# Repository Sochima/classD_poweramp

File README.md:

# classD_poweramp
Schematic and PCB files of a 15 W stereo Class D power amplifier

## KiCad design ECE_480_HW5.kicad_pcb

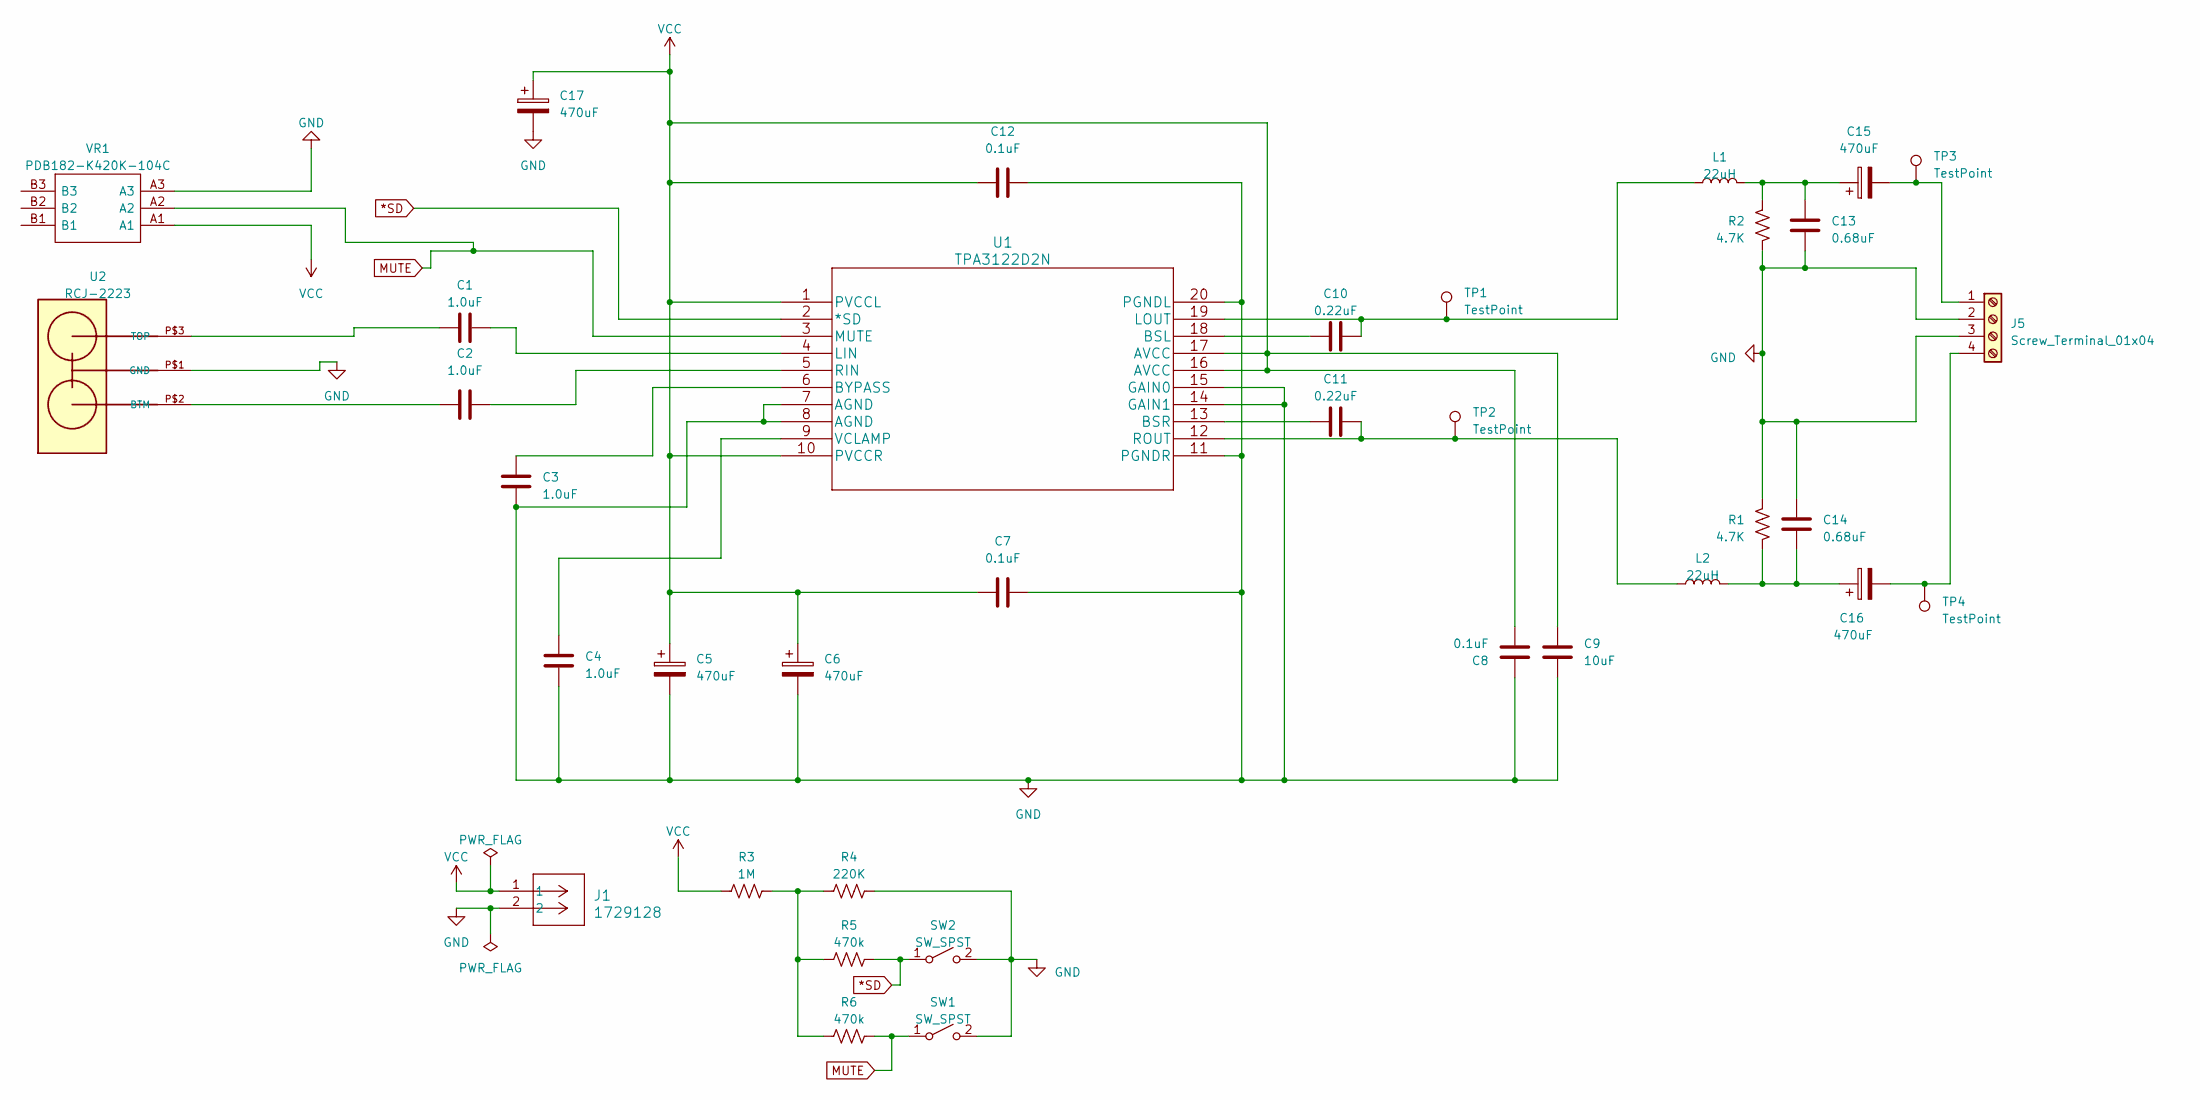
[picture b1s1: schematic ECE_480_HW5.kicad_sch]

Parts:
C1, C2, C3, C4: 1.0uF; CP_Axial_L10.0mm_D4.5mm_P15.00mm_Horizontal
C5, C6, C15, C16, C17: 470uF; CP_Radial_D7.5mm_P2.50mm
C7, C8, C12: 0.1uF; CP_Axial_L10.0mm_D4.5mm_P15.00mm_Horizontal
C9: 10uF; CP_Axial_L10.0mm_D4.5mm_P15.00mm_Horizontal
C10, C11: 0.22uF; CP_Axial_L10.0mm_D4.5mm_P15.00mm_Horizontal
C13, C14: 0.68uF; CP_Axial_L10.0mm_D4.5mm_P15.00mm_Horizontal
J1: 1729128; CONN_1729128_PXC
J5: Screw_Terminal_01x04; TerminalBlock_bornier-4_P5.08mm
L1, L2: 22uH; L_Axial_L16.0mm_D6.3mm_P20.32mm_Horizontal_Fastron_VHBCC
R1, R2: 4.7K; R_Axial_DIN0207_L6.3mm_D2.5mm_P10.16mm_Horizontal
R3: 1M; R_Axial_DIN0207_L6.3mm_D2.5mm_P10.16mm_Horizontal
R4: 220K; R_Axial_DIN0207_L6.3mm_D2.5mm_P10.16mm_Horizontal
R5, R6: 470k; R_Axial_DIN0207_L6.3mm_D2.5mm_P10.16mm_Horizontal
SW1, SW2: SW_SPST; SW_DIP_SPSTx01_Slide_9.78x4.72mm_W7.62mm_P2.54mm
TP1, TP2, TP3, TP4: TestPoint; TestPoint_THTPad_2.0x2.0mm_Drill1.0mm
U1: TPA3122D2N; N20
U2: RCJ-2223; DUALRCA
VR1: PDB182-K420K-104C; PDB182K420P204A2; Mouser Part Number 652-PDB182K420K104C

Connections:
*SD: R5.2, SW2.1 (A), U1.2 (*SD)
GND: C3.1, C4.2, C5.2, C6.2, C7.2, C8.1, C9.2, C12.2, C13.1, C14.2, C17.2, J1.2, J5.2, J5.3, R1.1, R2.2, R4.2, SW1.2 (B), SW2.2 (B), U1.7 (AGND), U1.8 (AGND), U1.11 (PGNDR), U1.14 (GAIN1), U1.15 (GAIN0), U1.20 (PGNDL), U2.P$1 (GND), VR1.A3
MUTE: R6.2, SW1.1 (A), U1.3 (MUTE), VR1.A2
unnamed: C13.2, C15.1, L1.2, R2.1
unnamed: C14.1, C16.1, L2.2, R1.2
unnamed: C15.2, J5.1, TP3.1
unnamed: C16.2, J5.4, TP4.1
unnamed: R3.2, R4.1, R5.1, R6.1
unnamed: C10.1, U1.18 (BSL)
unnamed: C11.1, U1.13 (BSR)
unnamed: C3.2, U1.6 (BYPASS)
unnamed: C1.2, U1.4 (LIN)
unnamed: C10.2, L1.1, TP1.1, U1.19 (LOUT)
unnamed: C2.2, U1.5 (RIN)
unnamed: C11.2, L2.1, TP2.1, U1.12 (ROUT)
unnamed: C4.1, U1.9 (VCLAMP)
unnamed: C2.1, U2.P$2 (BTM)
unnamed: C1.1, U2.P$3 (TOP)
VCC: C5.1, C6.1, C7.1, C8.2, C9.1, C12.1, C17.1, J1.1, R3.1, U1.1 (PVCCL), U1.10 (PVCCR), U1.16 (AVCC), U1.17 (AVCC), VR1.A1

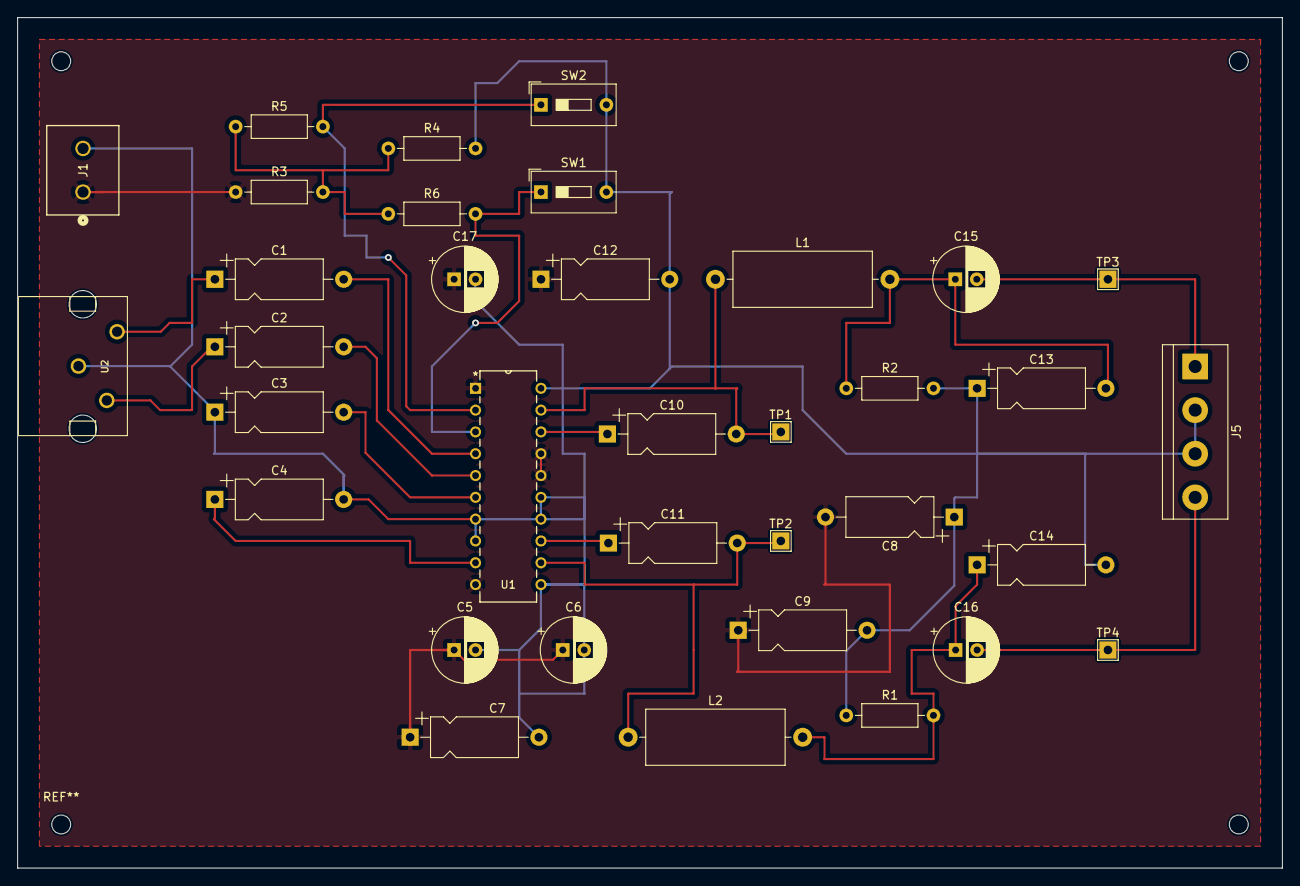
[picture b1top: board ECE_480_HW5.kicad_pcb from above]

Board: 2 copper layers, 147.3 x 99.1 mm, 35 parts (0 on the bottom side), 19 nets.

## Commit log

2024-09-10 Added PCB and Schematic files
2024-09-10 Rename ECE_480_HW5.kicad_pcb to ClassD_PowerAmp.kicad_pcb
